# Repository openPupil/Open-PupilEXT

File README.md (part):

<div align="center">
  
</div><br/>
<div align="center">

</div>

<p align="center">
    &nbsp;
  
  </p>

# PupilEXT: flexible open-source platform for high resolution pupillometry in vision research

This repository provides the official implementation of a free pupillometry cross-platform (MacOS, Windows, Linux) system called PupilEXT proposed in the article *"PupilEXT: flexible open-source platform for high resolution pupillometry in vision research"* authored by Babak Zandi, Moritz Lode, Alexander Herzog, Georgios Sakas and Tran Quoc Khanh from the Technical University of Darmstadt.<br/>

PupilEXT can record eye images using a stereo camera system or a single camera to measure the pupil diameter in real-time. Additionally, it is possible to analyse externally-recorded images without connected cameras through the PupilEXT interface.<br/>

We aimed to provide a professional open-source pupillometry measurement platform, making an easy and inexpensive entry into pupil research for interdisciplinary research groups possible. PupilEXT integrates high-resolution industrial cameras from Basler. The pupil detection itself can be performed with one of the state-of-the-art open-source algorithms, Starburst [[1\]](#1), Swirski2D [[2\]](#2), ExCuSe [[3\]](#3), ElSe [[4\]](#4), PuRe [[5\]](#5), and PuReST [[6\]](#6).<br/>

-----

<div align="center">
<a style="font-weight:bold" href="https://www.frontiersin.org/articles/10.3389/fnins.2021.676220/abstract">[Paper]</a>
<a style="font-weight:bold" href="https://www.frontiersin.org/articles/10.3389/fnins.2021.676220/abstract">[Supplementary materials]</a>
</div>

-----

**Features of PupilEXT**

- [x]  High resolution pupillometry
- [x]  Real-time pupillometry
- [x]  Professional graphical user interface programmed with QT/C++
- [x]  Supporting stereo camera setups
- [x]  Supporting single camera setups
- [x]  Supporting Basler branded cameras (USB3). Tested with Basler acA2040-120um and acA1300-200um.
- [x]  Offline pupillometry with externally recorded images
- [x]  Cross-platform software: MacOS, Windows, Linux
- [x]  Intgrates six leading open-source pupil detection algorithms: Starburst [[1\]](#1), Swirski2D [[2\]](#2), ExCuSe [[3\]](#3), ElSe [[4\]](#4), PuRe [[5\]](#5), and PuReST [[6\]](#6).

For initial testing, we recommend using the provided demo datasets. See section 2.4 in this repository. Pay attention to the image playback speed under "preference" (see video tutorial) if you are on a laptop with low computational power.

**Questions?**

If you have new ideas, questions or want to discuss some extended topics, please use our discussion forum:
https://github.com/openPupil/Open-PupilEXT/discussions

**!! NEW 08/2024 !!: Release of PupilEXT v0.1.2**

A new branch called Experimental-Community-Version has been created (see https://github.com/openPupil/Open-PupilEXT/tree/Experimental-Community-Version) to support community additions. In this new branch PupilEXT v0.1.2 is available. Its maintainers are Gábor Bényei and Attila Boncsér. For further information check out the community [README](https://github.com/openPupil/Open-PupilEXT/tree/Experimental-Community-Version). More informations about the new features are also available here: https://github.com/openPupil/Open-PupilEXT/discussions/27

**!! NEW 04/2022 !!: A Python version of PupilEXT is now available.**

Note that the Python package of PupilEXT is currently in the experimental stage.

Link to the GitHub repo of PyPupilEXT: [https://github.com/openPupil/PyPupilEXT](https://github.com/openPupil/PyPupilEXT)

**!! NEW 12/2021 !!: Watch the video tutorials of PupilEXT that walk trough the interface**

**Tutorial 1/3:** Stereo camera recording<br/>
https://vimeo.com/564556788

**Tutorial 2/3:** Single camera recording<br/>
https://vimeo.com/564776313

**Tutorial 3/3:** External image analysis<br/>
https://vimeo.com/564778587

## 1. Overview
PupilEXT is a real-time pupillometry software whose graphical user interface is mainly programmed using C++ (QT. 5.15) and can be used to integrate high-resolution industrial cameras for online measurements. This Repository provides a guide on how to install, set up and use the system for pupillometry. Before using the PupilEXT framework, we recommend reading the work *"PupilEXT: flexible open-source platform for high resolution pupillometry in vision research"*.

### 1.1 Pupillometry setup configuations
With PupilEXT, you can detect the pupil diameter with three different setup configurations (see Figure). In the stereo camera configuration, the pupil diameter can be recorded directly in millimetres through an internal triangulation procedure. In the simplest case, only one camera must be connected for measuring the pupil diameter in pixels. The conversion from pixels to mm can then manually be performed using a circular reference object. If no camera is available, PupilEXT offers the possibility to load externally recorded images for offline analysis. The externally acquired images can be treated as a live feed, unlocking the full functionality of PupilEXT.

### 1.2 Hardware and software requirements
Depending on which setup configuration is used, additional hardware components must be purchased. Below is a list of components with which our demo system was built. In general, the USB3 Basler branded camera should be compatible with PupilEXT, as we use Pylon. For offline analysis with externally captured images, none of the listed hardware components is necessary. In any case, the [Pylon Camera Software Suite](https://www.baslerweb.com/de/produkte/software/basler-pylon-camera-software-suite/) from Basler must be installed on your system, as the drivers are needed to start PupilEXT, even if no camera(s) is connected. Check out our publication if you need additional information on how to build the hardware system.

**Components: Stereo camera configuration**

- 2 x Basler acA2040-120um (USB3 cameras)
- 2 x KOWA LM50JC3M2 (2/3" C-Mount lenses)
- 2 x Schneider IF 092 SH 27.0 (Filters)
- 2 x H06S Power I/O Cable
- 1 x STM32 Nucleo F767ZI or similar (Hardware trigger)
- 1 x IR-illumination (Recommended)

**Components: Single camera configuration**

- 1 x Basler acA2040-120um (USB3 cameras)
- 1 x KOWA LM50JC3M2 (2/3" C-Mount lense)
- 1 x Schneider IF 092 SH 27.0 (Red & NIR Color Filter)
- *1 x H06S Power I/O Cable (Optional)*
- *1 x STM32 Nucleo F767ZI or similar (Optional)*
- 1 x IR-illumination (Recommended)

We also tested the system with a Basler acA1300-200um camera model. To build a cheap pupillometry system, you can also have a look to the Basler dart series cameras, which cost approximatley 120 Euro. Note that we did not test PupilEXT with a dart series camera from Basler, but it should work as we use the standard Pylon library from Basler to communicate with the USB3 cameras.

Please use our discussion forum to share your ideas, setup and experience with PupilEXT with other community members:

https://github.com/openPupil/Open-PupilEXT/discussions

## 2. Getting started: The easy way
### 2.1. Installation on MacOS (macOS 10.15 or later)
The direct installation requires that you have macOS 10.15 or later installed on your machine. If this is not the case, you need to build PupilEXT from source, as the provided pre-build binaries in this section will only work on macOS 10.15 or later.

**Step 1: Download and install the Pylon Camera Softwware**

Download the Pylon Camera Software Suite (*.dmg) from the Basler Website:

https://www.baslerweb.com/de/vertrieb-support/downloads/downloads-software/

We tested PupilEXT with **Pylon 6.1.2.** (on Windows only **Pylon 6.0.1.** works, see the Win instructions below). If the Pylon installation does not start because of a security warning from Apple: Open the system preferences from macOS, click on "security & privacy" and press "Open Anyway" under the "General" tab. During the Pylon installation, ensure that a complete installation is carried out with the C++ binaries (Important!). For this, you need to choose the "custom" profile and activate all checkboxes under "Pylon runtime" and "SDKs". The Pylon library is necessary for PupilEXT to control and communicate with Basler branded cameras. The installation is also needed if no camera is connected, as the Basler drivers are part of the software.

Please test your Baslers camera(s) with the installed Pylon Viewer from Basler (see [Basler-Documentation: Pylon Viewer](https://docs.baslerweb.com/overview-of-the-pylon-viewer)) before driving the camera(s) with PupilEXT.

**Step 2: Download and run PupilEXT**

We have built and deployed PupilEXT for macOS 10.15 or later. You only need to download PupilEXT and open it. If you run into security warnings from Apple, you need to open the system preferences, click on "security & privacy" and then press "Open Anyway" under the "General" tab.

Download PupilEXT Version 0.1.1 Beta (MAC) from the release page of the project's GitHub repository:

https://github.com/openPupil/Open-PupilEXT/releases/tag/v0.1.1-beta

After you have downloaded the software, you can open the dmg file and run PupilEXT (see animation). We tested the program on a fresh installed Macbook Pro (Intel) with macOS Big Sur (Version 11.2.3) and a Mac Mini (Intel) with macOS Catalina (Version 10.15.7). If you run into issues, you need to build PupilEXT from source.

**Step 3: Testing with the demo datasets**

You can load the provided demo dataset (see section 2.4) into PupilEXT for initial testing and enjoying the features during offline analysis. We recommend watching the video tutorials (see section 2.5) of PupilEXT before using the provided eye images.

**Additional Information**

It should be noted that the PupilEXT software is not designed for the dark-mode of macOS, as the icons in the quick-toolbar are colored with black lines. Therefore, the icons will not be visible when running PupilEXT in dark mode. We recommend to use the software only in light-mode of macOS.

### 2.2. Installation on Windows 10 (64 bit)
**Step 1: Download and install the Pylon Camera Softwware**

Download the Pylon Camera Software Suite (*.exe) from the Basler Website:

https://www.baslerweb.com/de/vertrieb-support/downloads/downloads-software/

We tested PupilEXT with **Pylon 6.0.1.** on several fresh installed Windows 10 (64 bit) machines. Only the **Pylon 6.0.1.** version works with PupilEXT, as Windows is a diva. During the Pylon installation, ensure that a complete installation is carried out with the C++ binaries (Important!). For this, you need to choose the "custom" profile and activate all checkboxes under "Pylon runtime" and "SDKs". The Pylon library is necessary for PupilEXT to control and communicate with Basler branded cameras. The installation is also needed when no camera is connected, as the Basler drivers are part of the software.

Please test your camera with the installed Pylon Viewer from Basler (see [Basler-Documentation: Pylon Viewer](https://docs.baslerweb.com/overview-of-the-pylon-viewer)) before driving the cameras with PupilEXT.

**Step 2: Download and run PupilEXT**

For Windows, we have already built the software so that PupilEXT can simply be downloaded and will start without any further dependencies. Unpack the downloaded zip file and open PupilEXT.exe. It should run, as we tested it on several systems. However, if you run into unknown issues, you need to build PupilEXT from source (see instructions below).

Download PupilEXT Version 0.1.1 Beta (Windows) from the release page of the project's GitHub repository:

https://github.com/openPupil/Open-PupilEXT/releases/tag/v0.1.1-beta

**Step 3: Testing with the demo datasets**

You can load the provided demo dataset (see section 2.4) into PupilEXT for initial testing and enjoying the features during offline analysis. We recommend watching the video tutorials (see section 2.5) of PupilEXT before using the provided eye images.

### 2.3. Setup the microcontroller for the stereo camera configuration
A microcontroller is necessary if a real-time online pupil measurement should be carried out with a stereo camera system. The microcontroller has the task of generating a so-called electrical hardware-trigger, which is used to trigger the image acquisition on the camera (see [Basler-Documentation: Triggering](https://docs.baslerweb.com/triggered-image-acquisition)). The electrical hardware-trigger consists of a timed voltage signal of 3.3 V, which is applied to one of the camera's GPIO-Pins. If a sequence of images need to be acquired with a stable FPS, the hardware-trigger is a PWM-signal with a fixed frequency (see [Basler-Documentation: Trigger-Types](https://docs.baslerweb.com/trigger-selector) and [Basler-Documentation: GPIO Lines](https://docs.baslerweb.com/general-purpose-io-(gpio)-lines)). The advantage of acquiring images through a hardware-trigger signal is that the electrical signal can be connected parallel to both cameras, leading to a highly synchronized image recording. Synchronous image acquisition from both cameras is essential in a stereo camera system; otherwise, the conversion from pixels to mm is not reliable. The PupilEXT software uses a hardware-trigger from an external microcontroller (STM32 Nucleo) to acquire images from the stereo camera system. If you only want to use a single camera for pupil measurement, section 2.3 is not relevant for you.

In this way, the image capture process is as follows: The PupilEXT software sends a command (Protocol) to the microcontroller via USB (uart), aiming to start a logical hardware-trigger signal, which is transmitted from the microcontroller to the camera(s). The captured images are passed directly from the camera to PupilEXT via USB3. In continuous shooting, PupilEXT sends a command to let the microcontroller generate a continuous PWM signal, so there is no need for a single command for each trigger signal. This procedure is standard for all professional stereo camera systems. Hardware trigger signals can also be generated from the camera itself, but there is a risk that due to internal delays, the images will not be captured synchronously. Therefore, adding an external signal generator increases the stability of the system.

Since a standardised protocol between the PupilEXT software and the microcontroller is required, we have uploaded the corresponding embedded code in this repository in [``Misc/Microcontroller/STMNucleo_F767ZI``](Misc/Microcontroller/STMNucleo_F767ZI) and [``Misc/Microcontroller/STMNucleo_L432KC``](Misc/Microcontroller/STMNucleo_L432KC). The embedded projects were created using PlatformIO in Visual Studio Code. You can use either an STM32 Nucleo F767ZI or STM32 Nucleo L432KC microcontroller to flash our provided code to the microcontroller. Alternatively, you can use your own microcontroller, but you must pay attention to the communication protocol (see our publication).

We used the [Mbed 5 framework](https://os.mbed.com) for programming the STM32 Nucleo microcontroller. To simplify the flashing process for you, we highly recommend flashing the microcontroller using [Mbed Studio](https://os.mbed.com/studio/), as this is more user-friendly. Below is a step-by-step guide on how to flash the microcontroller with Mbed Studio.

**Step 1: Installation of Mbed Studio**

Download and install Mbed Studio. A free account is required before you can use it.

https://os.mbed.com/studio/

**Step 2: Flash the microcontroller**

Create a new project inside Mbed Studio and select your connected microcontroller from the list. In the following, we assume that you are using an STM32 Nucleo L432KC. Be sure to select Mbed OS 5 as a template from the list. You can select an empty programme as template. In the fresh created main.cpp file, paste the below-listed code and press the play button in Mbed Studio (Build profile: Release) to flash the microcontroller. If you are using an STM32 Nucleo F767ZI, use another code from the file [Misc/Microcontroller/STMNucleo_F767ZI/src/main.cpp](Misc/Microcontroller/STMNucleo_F767ZI/src/main.cpp), as the pin assignment is different.

```c++
#include "RawSerial.h"
#include "mbed.h"
#include <string>
#include <stdio.h>
#include <stdlib.h>

#define BUFF_LENGTH 15
#define BAUDRATE 115200

#define TX_PIN USBTX
#define RX_PIN USBRX

#define LED_PIN_1 LED1
#define Trigger_Pin PB_0

RawSerial pc(TX_PIN, RX_PIN);
volatile char rx_buf[BUFF_LENGTH];
Timer timer_Stopper;

DigitalOut LED_Green(LED_PIN_1);
DigitalOut Trigger(Trigger_Pin);
Ticker myTick;

// Global Values
char M_or_T; // T = Manually Trigger Mode
uint32_t Manually_Values[2];
uint32_t Automatic_Values[1];

volatile int flag_1 = 0;
volatile int flag_2 = 0;
int LED_ticker = 0;
int Threshold_Ticker = 0;
int STOP = 0;

void onTick() {
  LED_Green = !LED_Green;
  Trigger = !Trigger;
  LED_ticker++;
  if (LED_ticker >= 2 * Threshold_Ticker) {
    myTick.detach();
    LED_Green = 0;
    Trigger = 0;
  }
  if (STOP == 1) {
    myTick.detach();
    LED_Green = 0;
    Trigger = 0;
  }
}

void serialCb() {

  char *pch;
  pch = strtok((char *)rx_buf, "X");

  M_or_T = *pch;

  if (M_or_T == 'T') {
    pch = strtok(NULL, "X");
    Manually_Values[0] = atoi(pch);

    pch = strtok(NULL, "X");
    Manually_Values[1] = atoi(pch);
  }

  switch (M_or_T) {

  case 'T':
    Threshold_Ticker = Manually_Values[0];
    STOP = 0;
    LED_ticker = 0;
    myTick.attach_us(&onTick, Manually_Values[1]);
    break;

  case 'S':
    STOP = 1;
    break;

  default:
    break;
  }
}

void callback() {
  if (pc.getc() == '<') {
    pc.putc('<');
    for (int i = 0; i < 20; i++) {

      rx_buf[i] = pc.getc();

      if (rx_buf[i] != '>') {
        pc.putc(rx_buf[i]);
      }

      if (rx_buf[i] == '>') {
        pc.putc('>');
        pc.putc('\n');
        flag_1 = 1;
        break;
      }
    }
  }
}

int main() {
  LED_Green = 0;
  LED_ticker = 0;
  Trigger = 0;
  pc.baud(115200);
  pc.attach(&callback, Serial::RxIrq);
  pc.printf("Program started! \n");

  while (1) {
    if (flag_1 == 1) {
      serialCb();
      flag_1 = 0;
    }
  }
}
// STM32 Nucleo L432KC flashing code
// The provided code for the STM32 Nucleo is licensed under the MIT
// See the lincense file in this repostory:
// Microcontroller/STMNucleo_L432KC/LICENSE
```

**Step 3: Wire the components together:**

Plug the two purchased I/O cables (see section 1.2: Hardware requirements) into the I/O connector of camera 1 and 2. At the open end of the I/O cable are the respective 6 I/O lines of the camera. PIN 1, corresponding to Line 3 of the I/O cable can be used to apply a logical hardware trigger signal to the Basler acA2040-120um camera. Please read the documentation and warnings of your camera regarding the I/O PINs, otherwise you may damage your camera if the wrong voltage values are used (see [Basler-Manual: GPIO Lines](https://docs.baslerweb.com/general-purpose-io-(gpio)-lines)). Pay attention to the correct PIN numbers of the I/O connector and check the camera's documentation to see which I/O PIN is the correct one for your case: https://docs.baslerweb.com/aca2040-120um

Connect the respective I/O line of camera 1 and camera 2 in parallel with the trigger PIN on the microcontroller. If you have used our embedded code to flash the microcontroller, it is PIN ``PB_0`` on the STM32 Nucleo L432KC or PIN ``PC_6`` on the STM32 Nucleo F767ZI. You can check where the PIN is located on the board by checking the Mbed webpage:

Pinout sketch STM32 Nucleo L432KC: https://os.mbed.com/platforms/ST-Nucleo-L432KC/

Pinout sketch STM32 Nucleo F767ZI: https://os.mbed.com/platforms/ST-Nucleo-F767ZI/

We recommend verifying that the microcontroller has been successfully flashed. To do this, you can enter the following command ``<TX10X1000000>`` (Protocol: ``<T X Count_of_Trigger X Time_Trigger_on_us>``) in a serial monitor (Baudrate: 115200). For example, when using the protocol ``<TX5X1000000>``. This command will flash the green led 5 times at 1 Hz. For this, copy&paste **everything inside the highlighted area `` ``** to the serial monitor. As serial communication interace, either use the integrated serial monitor of Mbed Studio or another one like HWMonitor or [CoolTerm](https://freeware.the-meiers.org). The command ``<TX10X1000000>`` should start a flashing green LED (10 times) on the microcontroller, with a turn-on time of 1000000 microseconds in each cycle. Since the hardware-trigger PIN of the microcontroller is "connected" to the LED, it signifies that the PC-to-microcontroller communication and the signal generation are working. Additionally, the trigger signal can be measured using an oscilloscope.

Once the microcontroller's correct operation has been checked, the cameras can be connected to the microcontroller and the PC via USB. Simultaneously, the hardware trigger PIN of the microcontroller should be connected in parallel with GPIO PINs of camera 1 and camera 2. Do not forget to connect the GND line of the camera to the GND PIN of the microcontroller. The figure in [``Misc/img/PupilEXT_Measuremtn_Setups.png``](Misc/img/PupilEXT_Measuremtn_Setups.png) illustrates the setup of a stereo camera configuration. After the connection has been made correctly, the PupilEXT software can be started to begin measuring the pupil diameter through the stereo camera system.

### 2.4. Demo dataset for offline analysis
We provide three different recorded datasets containing eye images that can be analysed using PupilEXT. This should give users the possibility to work directly with the software PupilEXT. The first two data sets were recorded using a single camera. Data set number 3 was recorded with a stereo camera system and is used in the video tutorial of PupilEXT (see section 2.5). The images were acquired directly with PupilEXT, as we offer the feature to record images for later offline measurement of the pupil diameter without connected cameras. The data set is suitable for playing around with PupilEXT and getting a first impression.

We stored the demo data in the TUdatalib repository: https://tudatalib.ulb.tu-darmstadt.de/handle/tudatalib/2929

| Description | Preview | Download-Link | File-size |
| :---         |     :---:      |          :---- |         :---: |
| Recorded with a single camera under natural light with a filter in front of the lens. Dataset is without a calibration file. |  | [Download dataset 1](https://tudatalib.ulb.tu-darmstadt.de/bitstream/handle/tudatalib/2929/Single_camera_recording_1.zip?sequence=1&isAllowed=y) | 1.2 Gb |
| Recorded with a single camera under natural light without a filter in front of the lens. Dataset is without a calibration file |  | [Download dataset 2](https://tudatalib.ulb.tu-darmstadt.de/bitstream/handle/tudatalib/2929/Single_camera_recording_2.zip?sequence=2&isAllowed=y) | 600 Mb |
| Recorded using a stereo camera system with IR-illumination and a filter in front of the lens. Calibration files are available and loaded to PupilEXT (see instructions below). |  | [Part 1](https://tudatalib.ulb.tu-darmstadt.de/bitstream/handle/tudatalib/2929/Stereo_camera_recording_Part_1.zip?sequence=3&isAllowed=y)<br>[Part 2](https://tudatalib.ulb.tu-darmstadt.de/bitstream/handle/tudatalib/2929/Stereo_camera_recording_Part_2_CAM0.zip?sequence=4&isAllowed=y)<br>[Part 3](https://tudatalib.ulb.tu-darmstadt.de/bitstream/handle/tudatalib/2929/Stereo_camera_recording_Part_3_CAM1.zip?sequence=5&isAllowed=y) | ~10 Gb |

**Instructions on how to use the stereo camera demo data:**
The data set is divided into three parts. Please download all three files first. Part 1 (``Stereo_camera_recording_Part_1``) is the main folder containing the two subfolders ``Calibration_Files`` and ``Stereo_Images``. The ``Stereo_Images`` subfolder is currently empty and needs to be filled with the demo images of ``cam 0`` and ``cam 1``. For this, download Part 2 (``Stereo_camera_recording_Part_2_CAM0``) and Part 3 (``Stereo_camera_recording_Part_3_CAM1``). Unzip the two folders and rename the folder ``Stereo_camera_recording_Part_2_CAM0`` to ``0`` and also rename folder ``Stereo_camera_recording_Part_3_CAM1`` to ``1``. Move the renamed folder ``0`` and ``1`` into the subfolder ``Stereo_Images`` of the main folder ``Stereo_camera_recording_Part_1`` (Part 1). In PupilEXT, you only need to choose the subfolder Stereo_Imagesas image source. The folder ``0`` and ``1`` will be automatically assigned to ``cam 0`` and ``cam 1``. The individual calibration files are in the subfolder ``Calibration_Files``. You only need to choose the stereo calibration file and not the single calibration files for each camera (see video tutorials).

**Note on externally acquired images**

When loading images to PupilEXT for offline analysis, take care of proper file names. For example, if you label your files with sequenced numbers such as 1.png, 2.png, 3.png, 4.png, 5.png, 6.png, 7.png, 8.png, 9.png, 10.png, 11.png, you will run into issues, as the order of the images will be changed to 1.png, 10.png, 11.png, 2.png, ...

It is better to label the images with 001.png, with the time stamp in milliseconds or similar. If you recorded the images with PupilEXT, everything is labelled correctly as we use the timestamp in milliseconds as filenames. The provided demo datasets are recorded with PupilEXT.

### 2.5 Notes about the pupil detection acuracy

The pupil detection can be determined in PupilEXT with one of the six open-source pupil detection methods Starburst [[1\]](#1), Swirski2D [[2\]](#2), ExCuSe [[3\]](#3), ElSe [[4\]](#4), PuRe [[5\]](#5), and PuReST [[6\]](#6). The respective algorithm can be selected directly within the pupillometry interface. A pupil measurement's accuracy depends on the applied detection algorithm if the image quality and composition are ideal. Each pupil detection algorithm has a certain number of parameters (constants) that the user must set.  For instance, at least the minimum or maximum possible pupil diameter must be adjusted, which can depend on the image's resolution. In PupilEXT, we offer the possibility to adjust the parameters of an applied detection algorithm, leading to more freedom in increasing the measurement accuracy. The original publications' standard parameters are usually not ideal for all measurement settings and should be adjusted if the detection rate is not good enough.

The accuracy can also be increased by selecting a specific region of interest (ROI) in the image. In this way, the algorithm no longer needs to perform pupil detection over the entire image. A smaller ROI size also reduces the calculation time, allowing a higher framerate in real-time measurements. We provide different preset settings for the algorithms` parameters which are dependent on the used ROI size. However, we highly recommend using the PuRe or PuReST algorithm, as it needs only three parameters. Furthermore, these two pupil detection algorithms are considered both the fastest and accurate in the literature and are part of the amazing open-source eye-tracking software EyeRecToo [[7\]](#7). According to our preliminary investigations, the Swirski algorithm can provide better results, as it does not downscale the image before a pupil detection. The downside is that it needs a higher calculation time and has a higher number of parameters. There is the risk that the parameters do not match the image composition, leading to poor pupil detection accuracy.

### 2.5. How to use PupilEXT ?
Three videos are provided to illustrate the handling and the features of the *PupilEXT* software. The first video introduces the *PupilEXT* software in stereo vision mode. The second video shows how the pupillometry can be carried out by using a single camera. The third video shows how pupillometry can be carried out with existing eye images without connected cameras.

**Video Tutorial 1 – Stereo camera setup:** https://vimeo.com/564556788

**Video Tutorial 2 – Single camera setup:** https://vimeo.com/564776313

**Video Tutorial 3 – Offline analysis:** https://vimeo.com/564778587

## 3. Build PupilEXT from source: The advanced way

If you would like to contribute to this project, extend PupilEXT with custom functions, or the provided binaries do not work on your machine, building PupilEXT on your machine is necessary. The annoying part of compiling C++ projects is the integration of third-party libraries into a project. For this, you have three options: (i) use a system package manager like brew to download and build third-party libraries; (ii) download the libraries without a package manager and build it; (iii) integrating the libraries directly into the project.

If you want to stick with option (ii) you are a professional C++ developer and do not need this tutorial. Option (i) is preferable if you have several C++ projects on your machine and want to share the libraries between the projects, saving disc space (see section 3.1 and section 3.2). However, we highly recommend option (iii), which has the advatange that the integration of thirdparty libraries is fully automated(see section 3.0). You should have intermediate knowledge of C++ programming and CMake before you follow this tutorial, as we provide no warranty.

PupilEXT need the following libraries: Boost 1.75-0_2, Ceres 2.0.0, Eigen 3.3.9, OpenCV 4.5.1_3, QT 5.15.0, [spii](https://github.com/PetterS/spii), tbb, pylon 6.

**Important Note 1:** When using Boost@1.76 or higher, you will run into compiling issues, as boost::math::sign will not work, which is used by one of the pupil detection methods.

**Important Note 2:** If you want to follow option (i) or (ii)  you need to remove the 'vcpkg.json' file and the '.vscode' folder.

### 3.0 Build PupilEXT with vcpkg manifest (recommended)

The PupilEXT project contains a vcpkg.json file in which all the required C++ libraries are defined. To download and build the libraries, we use the package management software vcpkg (https://vcpkg.io/en/index.html). We have placed the vcpkg GitHub repository as a submodule under [``3rdparty/vcpkg``](3rdparty/vcpkg), meaning that the required libraries will be downloaded automatically to the PupilEXT project folder, regardless of your system. This has the advantage that the PupilEXT folder can be easily deleted when the C++ libraries are no longer needed. However, as the libraries are downloaded and built, care must be taken to ensure that at least 6 GB are available on the disc for the PupilEXT folder (on windows ~13 GB). However, the QT library and the Pylon drivers for the cameras will not be managed via vcpkg, so they have to be downloaded and installed manually (see step 1 and 2).

**Step 1: Download and install the latest Pylon Camera Softwware**

Download the Pylon Camera Software Suite (*.dmg-File) from the Basler Website:
https://www.baslerweb.com/de/vertrieb-support/downloads/downloads-software/

Important: You need to modify the [`Open-PupilEXT/cmake/FindPylon.cmake`](https://github.com/openPupil/Open-PupilEXT/blob/main/cmake/FindPylon.cmake) file according to the Pylon version before you start to build the project. Please read the latest post in this discussion for more information: https://github.com/openPupil/Open-PupilEXT/discussions/21

**Step 2: Download and install QT**

Download the QT from the website. Please install QT 5.15:
https://www.qt.io/download-open-source?hsCtaTracking=9f6a2170-a938-42df-a8e2-a9f0b1d6cdce%7C6cb0de4f-9bb5-4778-ab02-bfb62735f3e5

QT 6 or higher is currently not supported.

Update: On Mac QT 6.7.2 seems to work either.

**Step 3: Clone this repository**

Type into your terminal the following command

```shell
git clone --recurse-submodules https://github.com/openPupil/Open-PupilEXT.git
```

The ``--recurse-submodules`` option is important, as vcpkg is a submodule. Without this option, the 3rdparty folder will not contain vcpkg packet manager.

Open the ``CMakeLists.tx`` file in the PupilEXT root and change the following line, according to your installed QT, user name and cpu archteure.

```Cmake
set(QT_VERSION 5.15.2) # Change the version according to your installation
set(USER_NAME_MAC papillon) # Only necessary for macOS users, skip if you are on WIN

set(CMAKE_OSX_ARCHITECTURES_VALUE "arm64") # Options for cmake: arm64, x86_64 - needed for oneTBB
set(VCPKG_VALUE_ARCH "arm64-osx") # Options for vcpkg: arm64-osx, x64-osx
```

**Step 4: Decide which Editor to use**

Depending on which editor is used, the procedure is slightly different. We have created a summary of how to proceed if you want to use [Visual Studio Code](https://code.visualstudio.com), [CLion](https://www.jetbrains.com/clion/promo/?source=google&medium=cpc&campaign=11964013627&gclid=Cj0KCQjw-NaJBhDsARIsAAja6dPFpHIXmFeKhVv0qheHTki-WmG5DepDCzR0iWuYQqAXEM1eEAELpy4aApLsEALw_wcB) or [QT Creator](https://www.qt.io/product/development-tools) to start PupilEXT (see the below option 1 to 4).

**Option 1: Build with Visual Studio Code**

First, the following extensions must be downloaded in the editor for the procedure to work:

(1) C++ extension: https://marketplace.visualstudio.com/items?itemName=ms-vscode.cpptools

(2) Cmake extension: https://marketplace.visualstudio.com/items?itemName=twxs.cmake

(3) Cmake Tools extension: https://code.visualstudio.com/docs/cpp/cmake-linux

Then open the ``.vscode/settings.json`` file in the cloned PupilEXT folder with a text editor. The entry ``"VCPKG_TARGET_TRIPLET": "x64-osx"`` must be changed to ``"VCPKG_TARGET_TRIPLET": "x64-windows-static-md"`` if you have a Windows operating system. If you are on a Mac, leave the entry as it is. However, when using a Mac with apple silicon (e.g. M3 Max or similar) you need to change this entry to ``"VCPKG_TARGET_TRIPLET": "arm64-osx"``. Open the project folder with Visual Studio Code and build the project. If you press build for the first time, it may take a little longer, as the required libraries are downloaded and will build automatically. Make sure that you have enough disc space on your machine.

**Option 2: Build with CLion**

Open the project folder with CLion. Then some settings have to be made. For this, go to ``CLion > Preferences > Build, Execution, Deployment`` in the toolbar. Choose Debug and type in the Cmake options the following command:

```shell
-DVCPKG_TARGET_TRIPLET=x64-osx -DCMAKE_TOOLCHAIN_FILE=3rdparty/vcpkg/scripts/buildsystems/vcpkg.cmake
```
Note that `x64-osx` must be changed to `x64-windows-static-md`, if you are on a Windows machine. However, when using a Mac with apple silicon (e.g. M3 Max or similar) you need to change this entry to ``"VCPKG_TARGET_TRIPLET": "arm64-osx"``. Next, choose for the build directory, the following folder: ``build``. This is very important, as the CMakeLists.txt is adjusted to find the libraries in a folder called ``build``. By default, CLion will build the project in a folder called ``cmake-build-debug``, which will not work with the current CMakeLists.txt. Press okay and build the project. The C++ libraries will be downloaded and build automatically for you. The first run will take some time. Make sure that you have enough disc space.

**Option 3: Build with QT Creator**

QTCreator also supports CMake, which means that PupilEXT can also be opened there. As with CLion, only the following options need to be added:

```shell
-DVCPKG_TARGET_TRIPLET=x64-osx -DCMAKE_TOOLCHAIN_FILE=3rdparty/vcpkg/scripts/buildsystems/vcpkg.cmake
```

Note that `x64-osx` must be changed to `x64-windows-static-md`, if you are on a Windows machine. However, when using a Mac with apple silicon (e.g. M3 Max or similar) you need to change this entry to `"VCPKG_TARGET_TRIPLET": "arm64-osx"`. Next, choose for the build directory, the following folder: ``build``.

**Option 4: Build from terminal**

Open your terminal and type the following commands if you are on a Mac:

```shell
cd Open-PupilEXT

mkdir build

cd build

cmake .. -G "Unix Makefiles" -DCMAKE_BUILD_TYPE=Release -DVCPKG_TARGET_TRIPLET=x64-osx -DCMAKE_TOOLCHAIN_FILE=3rdparty/vcpkg/scripts/buildsystems/vcpkg.cmake

cmake --build . --config Release

./src/PupilEXT
```
Note that you need to change `-DVCPKG_TARGET_TRIPLET=x64-osx` to `"VCPKG_TARGET_TRIPLET": "arm64-osx"` if you have an apple silicon.

If you are on Windows 10  use these commands (not tested, but should be similar):

```shell
cd Open-PupilEXT

mkdir build

cd build

cmake .. -DCMAKE_BUILD_TYPE=Release -DVCPKG_TARGET_TRIPLET=x64-windows-static-md -DCMAKE_TOOLCHAIN_FILE=3rdparty/vcpkg/scripts/buildsystems/vcpkg.cmake

cmake --build . --config Release
```
Then, the executable will be available here ``/Open-PupilEXT-main/build/src/PupilEXT``.

Note, the option ``-DCMAKE_TOOLCHAIN_FILE=3rdparty/vcpkg/scripts/buildsystems/vcpkg.cmak`` makes sure to use the submodule as package manager and download the C++ libraries defined in the vcpkg.json file. The ``-DVCPKG_TARGET_TRIPLET=x64-os`` option is necessary to let vcpkg know which triplet your need. On Windows you need to change the tripplet to ``-DVCPKG_TARGET_TRIPLET=x64-windows-static-md``.

### 3.1 How to build from source on MacOS (outdated)

**Step 1: Download and install the latest Pylon Camera Softwware**

Download the Pylon Camera Software Suite (*.dmg-File) from the Basler Website:
https://www.baslerweb.com/de/vertrieb-support/downloads/downloads-software/

**Step 2: Download and install QT**

Download the QT from the website. Please install QT 5.15:
https://www.qt.io/download-open-source?hsCtaTracking=9f6a2170-a938-42df-a8e2-a9f0b1d6cdce%7C6cb0de4f-9bb5-4778-ab02-bfb62735f3e5

**Step 3: Install the package manager homebrew**

Homebrew is a package manager for macOS with which C++ libraries can be installed relatively easily via the terminal. Instructions on how to install Homebrew can be found here: https://brew.sh

To install homebrew , you can enter the following command in the macOS terminal.

```shell
/bin/bash -c "$(curl -fsSL https://raw.githubusercontent.com/Homebrew/install/HEAD/install.sh)"
```

**Step 4: C++ Libraries**

Now install the necessary C++ libraries for PupilEXT through homebrew. The Ceres library will be installed by OpenCV.

```shell
brew install cmake
brew install boost
brew install Eigen
brew install glog
brew install tbb
brew install opencv
```

**Step 5: Download and build the spii library**

An additional library called spii must be downloaded and built manually. This library is not included in Homebrew. First, go to the following GitHub repository and download it:

https://github.com/PetterS/spii

Open the downloaded folder ``spii-master`` with [CLion](https://www.jetbrains.com/clion/). By default, CLion is set to debug mode. Therefore, the release option must be added. For this, go to CLion > Preferences > Build, Execution, Deployment in the toolbar. Then press the + symbol under CMake, which automatically adds the release mode. You can then switch to release in the top right-hand corner of the CLion toolbar. You can now build the project. Simply go to Build > Build Project.

**Step 6: Add spii to PupilEXT**

The source files of PupilEXT are located here in Github under the PupilEXT folder. Download it from GitHub and create a new folder called ``PupilEXT/external`` in the main PupilEXT folder. In ``external/`` add another new folder called ``spii/``.

In the folder ``PupilEXT/external/spii`` you need to copy the spii build created in step 5. First go to ``spii-master/cmake-build-release`` and copy the folder ``spii-master/cmake-build-release/lib`` to ``spii-master``. Then copy all files inside the ``spii-master/`` folder into ``PupilEXT/external/spii``.

**Step 7: Build PupilEXT from source**

Now, open the PupilEXT project with CLion. In the file ``PupilEXT/CMakeLists.txt`` the paths must be updated so that the installed C++ libraries from step 4 can be correctly recognised. The complete content in ``PupilEXT/CMakeLists.txt`` can be removed and replaced by the following code snippet:

```cmake
cmake_minimum_required(VERSION 3.15)
project(PupilEXT)
set(CMAKE_CXX_STANDARD 17)

set(CMAKE_AUTOMOC ON)
set(CMAKE_AUTORCC ON)
set(CMAKE_AUTOUIC ON)

if(CMAKE_VERSION VERSION_LESS "3.7.0")
    set(CMAKE_INCLUDE_CURRENT_DIR ON)
endif()

set(CMAKE_MODULE_PATH ${CMAKE_MODULE_PATH} ${PROJECT_SOURCE_DIR}/cmake)
set(CMAKE_PREFIX_PATH ${CMAKE_PREFIX_PATH} "/Users/papillon/Qt/5.15.2/clang_64")
set(CMAKE_PREFIX_PATH ${CMAKE_PREFIX_PATH} "/usr/local/Cellar/glog/0.4.0")
set(CMAKE_PREFIX_PATH ${CMAKE_PREFIX_PATH} "/usr/local/include/gflags")
set(CMAKE_PREFIX_PATH ${CMAKE_PREFIX_PATH} "/Library/Frameworks/pylon.framework")
set(CMAKE_PREFIX_PATH ${CMAKE_PREFIX_PATH} "/usr/local/Cellar/tbb/2020_U3_1")

set(SPII_INSTALL_DIR "/Users/papillon/Desktop/PupilEXT/external/spii")
set(spii_INCLUDE_DIRS ${SPII_INSTALL_DIR}/include)
set(GLOG_INCLUDE_DIR "/usr/local/Cellar/glog/0.4.0/include")
set(EIGEN_INCLUDE_DIR "/usr/local/Cellar/eigen/3.3.9/include/eigen3/Eigen")
set(EIGEN3_INCLUDE_DIR "/usr/local/include/eigen3")
SET("OpenCV_DIR" "/usr/local/Cellar/opencv/4.5.1_3/lib/cmake/opencv4")
SET("TBB_DIR" "/usr/local/Cellar/tbb/2020_U3_1/lib/cmake/TBB")

if(CMAKE_BUILD_TYPE STREQUAL Debug)
    set(CMAKE_PREFIX_PATH ${CMAKE_PREFIX_PATH} "/usr/local/share/ceres-solver")
else()
    set(CMAKE_PREFIX_PATH ${CMAKE_PREFIX_PATH} "/usr/local/share/ceres-solver")
endif()

set(PYLON_HOME "/Library/Frameworks/pylon.framework")
set(PYLON_INCLUDE_DIR "/Library/Frameworks/pylon.framework/Headers")

find_package(Qt5 COMPONENTS Widgets Concurrent SerialPort Charts Svg PrintSupport REQUIRED)
find_package(OpenCV REQUIRED PATHS "/usr/local/Cellar/opencv/4.5.1_3")
find_package(Boost 1.72 REQUIRED)
find_package(TBB REQUIRED PATHS "${PROJECT_SOURCE_DIR}/external/tbb")
find_package(Eigen3 REQUIRED )
find_package(Ceres REQUIRED)
find_package(Pylon REQUIRED)
find_package(OpenGL REQUIRED)

set(TBB_LIBRARY_DEBUG "/usr/local/include/tbb")
set(TBB_LIBRARY_RELEASE "/usr/local/include/tbb")

find_library (spii_LIBRARY_RELEASE
        spii
        PATHS ${SPII_INSTALL_DIR}/lib/)
find_library (meschach_LIBRARY_RELEASE
        meschach
        PATHS ${SPII_INSTALL_DIR}/lib/)
if (spii_LIBRARY_RELEASE AND meschach_LIBRARY_RELEASE)
    set(spii_LIBRARIES ${spii_LIBRARY_RELEASE} ${meschach_LIBRARY_RELEASE})
else()
    set(spii_LIBRARIES "")
endif()

include_directories(${Qt5Core_INCLUDE_DIRS}
        ${OpenCV_INCLUDE_DIRS}
        ${Boost_INCLUDE_DIRS}
        ${TBB_INCLUDE_DIR}
        ${spii_INCLUDE_DIRS}
        ${EIGEN_INCLUDE_DIR}
        ${CERES_INCLUDE_DIRS}
        ${PYLON_INCLUDE_DIR}
        "singleeyefitter")

add_subdirectory (src)
add_subdirectory (singleeyefitter)

message(STATUS "")
message(STATUS "spii_LIBRARIES:\"${spii_LIBRARIES}\"")
message(STATUS "--- Include directories ---" )
message(STATUS " QT5Core_INCLUDE_DIRS: ${Qt5Core_INCLUDE_DIRS}" )
message(STATUS " OpenCV_INCLUDE_DIRS: ${OpenCV_INCLUDE_DIRS}" )
message(STATUS " Boost_INCLUDE_DIRS: ${Boost_INCLUDE_DIRS}" )
message(STATUS " TBB_INCLUDE_DIRS: ${TBB_INCLUDE_DIR}" )
message(STATUS " spii_INCLUDE_DIRS: ${spii_INCLUDE_DIRS}" )
message(STATUS " EIGEN_INCLUDE_DIR: ${EIGEN_INCLUDE_DIR}" )
message(STATUS " CERES_INCLUDE_DIRS: ${CERES_INCLUDE_DIRS}" )
message(STATUS " PYLON_INCLUDE_DIRS: ${PYLON_INCLUDE_DIR}" )
message(STATUS "---------------------------" )
message(STATUS "")
set(CMAKE_CXX_FLAGS "${CMAKE_CXX_FLAGS} -march=native -O3")
```

Make sure that all folder paths in the ``CMakelist.txt`` are adapted to your system. For instance, the path ``/Users/papillonmac/Qt/5.15.0/clang_64`` must be changed with the name of your user name and your specific QT version installed on your PC.

----

The described changes to the Pylon library in this section can be skipped, as we included in the updated CMakelists.txt the following code for macOS:

```cmake
set(PYLON_INCLUDE_DIR ${PYLON_INCLUDE_DIR} "/Library/Frameworks/pylon.framework/Headers")
    set(PYLON_INCLUDE_DIR ${PYLON_INCLUDE_DIR} "/Library/Frameworks/pylon.framework/Headers/GenICam")
```

**Old description (not needed):**

The last step is to change something in the Pylon library; otherwise, the library will not be found properly. For this, open the following folder on your computer: /Library/Frameworks/pylon.framework/Versions/A/Headers/GenICam. All files in this folder must be copied to /Library/Frameworks/pylon.framework/Versions/A/Headers.

---

Now, you should be able to start PupilEXT properly in CLion. Please remember to use the **release** option as in step 5; otherwise, PupilEXT will run in debug mode and will be significantly slower.

### 3.2 How to build from source on Windows 10

**Step 1: Install Visual Studio 2019**

C++ MFC must be installed during the installation. Additionally, the English language package must be included. Visual Studio can be downloaded from the following page:

https://visualstudio.microsoft.com/downloads/

**Step 2: Download and install the Pylon Camera Software**

Download the Pylon Camera Software Suite (*.dmg) from the Basler Website:
https://www.baslerweb.com/de/vertrieb-support/downloads/downloads-software/

**Step 3: Download and install QT**

Download the QT from the website. Please install QT 5.15. You need to add ``msvc2017_64`` during the installation:
https://www.qt.io/download-open-source?hsCtaTracking=9f6a2170-a938-42df-a8e2-a9f0b1d6cdce%7C6cb0de4f-9bb5-4778-ab02-bfb62735f3e5

**Step 4: Install the C++ package manager**

There is a C++ package manager from Microsoft for Windows, making it relatively easy to download libraries. For this, install the program ``vcpkg``. The instructions on how to install the package manager can be found on the following page:

https://docs.microsoft.com/de-de/cpp/build/install-vcpkg?view=msvc-160&tabs=windows

To install vcpkg type in your console the following commands:

```shell
git clone https://github.com/Microsoft/vcpkg.git
cd vcpkg
.\bootstrap-vcpkg.bat
```

**Step 5: Install the C++ Librarys**

Go to your console and use the following commands to install the C++ libraries:

```shell
vcpkg install boost:x64-windows
vcpkg install Eigen:x64-windows
vcpkg install ceres:x64-windows
vcpkg install glog:x64-windows
vcpkg install opencv:x64-windows
vcpkg install tbb:x64-windows
```

**Step 6: Download and build spii**

The spii library is not included in vcpkg. You need to build it manually. First, go to the following page and download the spii library from GitHub:

https://github.com/PetterS/spii

Then [CLion](https://www.jetbrains.com/clion/) can be used to open and build the spii library. Make sure that you use the 64 bit architecture. Then the folder ``spii-master/cmake-build-release/lib`` can be copied into the main folder ``spii-master/``. Lastly, copy the files inside ``spii-master/`` to ``PupilEXT/external/spii``.

**Step 7: Prepare the CMakelists file**

You can add the following code snippet to the file ``PupilEXT/CMakeLists.txt``  to let PupilEXT recognize vcpkg libraries. Make sure to adjust the appropriate paths and version numbers.

```cmake
cmake_minimum_required(VERSION 3.15)
project(PupilEXT)

set(CMAKE_AUTOMOC ON)
set(CMAKE_AUTORCC ON)
set(CMAKE_AUTOUIC ON)
if(CMAKE_VERSION VERSION_LESS "3.7.0")
    set(CMAKE_INCLUDE_CURRENT_DIR ON)
endif()

set(CMAKE_MODULE_PATH ${CMAKE_MODULE_PATH} ${PROJECT_SOURCE_DIR}/cmake)
set(CMAKE_PREFIX_PATH ${CMAKE_PREFIX_PATH} "C:/Qt/Qt5.13.1/5.10.0/msvc2017_64")
set(CMAKE_PREFIX_PATH ${CMAKE_PREFIX_PATH} "C:/vcpkg/installed/x64-windows")
set(GLOG_INCLUDE_DIR "C:/vcpkg/installed/x64-windows/include")
if(CMAKE_BUILD_TYPE STREQUAL Debug)
    set(CMAKE_PREFIX_PATH ${CMAKE_PREFIX_PATH} "C:/vcpkg/installed/x64-windows/debug")
else()
    set(CMAKE_PREFIX_PATH ${CMAKE_PREFIX_PATH} "C:/vcpkg/installed/x64-windows/include")
endif()

set(TBB_INCLUDE_DIR "C:/vcpkg/installed/x64-windows/include/tbb")
set(SPII_INSTALL_DIR "${PROJECT_SOURCE_DIR}/external/spii")
set(spii_INCLUDE_DIRS ${SPII_INSTALL_DIR}/include)
set(PYLON_HOME "C:/Program Files/Basler/pylon 6/Development/")
find_package(Qt5 COMPONENTS Widgets SerialPort Charts Svg PrintSupport REQUIRED)
find_package(OpenCV REQUIRED)
find_package(Boost 1.72 REQUIRED)
find_package(TBB REQUIRED PATHS "${PROJECT_SOURCE_DIR}/external/tbb")
find_package(Eigen3 REQUIRED )
find_package(Ceres CONFIG REQUIRED)
find_package(Pylon REQUIRED)
set(TBB_LIBRARY_DEBUG "${PROJECT_SOURCE_DIR}/external/tbb/lib/intel64")
set(TBB_LIBRARY_RELEASE "${PROJECT_SOURCE_DIR}/external/tbb/lib/intel64")

find_library (spii_LIBRARY_RELEASE
        spii
        PATHS ${SPII_INSTALL_DIR}/lib/)
find_library (meschach_LIBRARY_RELEASE
        meschach
        PATHS ${SPII_INSTALL_DIR}/lib/)
if (spii_LIBRARY_RELEASE AND meschach_LIBRARY_RELEASE)
    set(spii_LIBRARIES ${spii_LIBRARY_RELEASE} ${meschach_LIBRARY_RELEASE})
else()
    set(spii_LIBRARIES "")
endif()

include_directories(${Qt5Core_INCLUDE_DIRS}
        ${OpenCV_INCLUDE_DIRS}
        ${Boost_INCLUDE_DIRS}
        ${TBB_INCLUDE_DIR}
        ${spii_INCLUDE_DIRS}
        ${EIGEN_INCLUDE_DIR}
        ${CERES_INCLUDE_DIRS}
        ${PYLON_INCLUDE_DIR}
        "singleeyefitter")

add_subdirectory (src)
add_subdirectory (singleeyefitter)

message(STATUS "")
message(STATUS "spii_LIBRARIES:\"${spii_LIBRARIES}\"")
message(STATUS "--- Include directories ---" )
message(STATUS " QT5Core_INCLUDE_DIRS: ${Qt5Core_INCLUDE_DIRS}" )
message(STATUS " OpenCV_INCLUDE_DIRS: ${OpenCV_INCLUDE_DIRS}" )
message(STATUS " Boost_INCLUDE_DIRS: ${Boost_INCLUDE_DIRS}" )
message(STATUS " TBB_INCLUDE_DIRS: ${TBB_INCLUDE_DIR}" )
message(STATUS " spii_INCLUDE_DIRS: ${spii_INCLUDE_DIRS}" )
message(STATUS " EIGEN_INCLUDE_DIR: ${EIGEN_INCLUDE_DIR}" )
message(STATUS " CERES_INCLUDE_DIRS: ${CERES_INCLUDE_DIRS}" )
message(STATUS " Pylon_INCLUDE_DIRS: ${PYLON_INCLUDE_DIR}" )
message(STATUS "---------------------------" )
message(STATUS "")
set(CMAKE_CXX_FLAGS "${CMAKE_CXX_FLAGS} -march=native -O3")
```

**Step 8: Environment variables**

Add the bin folder of vcpkg and QT to the environment variables of Windows; otherwise, the libraries will not be found.

**Step 9: Build PupilEXT with CLion**

Before the programme can be build, some settings must be made in CLion:

1) File > Setting > Build, Execution, Deoployment > CMAKE under CMAKE options add the following parameter: --config Debug -DVCPKG_TARGET_TRIPLET=x64-windows -DCMAKE_TOOLCHAIN_FILE=C:/vcpkg/scripts/buildsystems/vcpkg.cmake

2) Then press the plus sign to add the release configuration. Add the following parameters to the release options:: --config Release -DVCPKG_TARGET_TRIPLET=x64-windows -DCMAKE_TOOLCHAIN_FILE=C:/vcpkg/scripts/buildsystems/vcpkg.cmake

3) The build architecture must be changed to amd64 under Toolchain, as the vcpkg libraries were also installed with 64 bit.

Next, the bin folders must be added to the path of CLION, as these are independent of the Windows environment variables. Under Run > Edit Configuration the paths to VCPKG and QT can be added:

```shell
C:\Qt\Qt5.13.1\5.10.0\msvc2017_64\bin
C:\vcpkg\installed\x64-windows\bin
```

In order to start the programme, the SPII DLL must be added to ``PupilEXT\cmake-build-debug\src``. If everything has been done correctly, you can now press Start and the software should open without any issues.

## 4. Misc

**Camera emulation**
For debugging porpuses, the Pylon SDK supports emulating camera devices that are then displayed as physical cameras in the PupilExt software. To activate the camera emulation, the system environment variable "PYLON_CAMEMU" needs to be set. The number of available emulator devices can be controlled by exporting the PYLON_CAMEMU environment variable. For example, ``export PYLON_CAMEMU=2``.

## 5. Known issues
see here https://github.com/openPupil/Open-PupilEXT/issues

## 6. Citation
Please consider to cite our work if you find this repository or our results useful for your research:

B. Zandi, M. Lode, A. Herzog, G. Sakas, and T. Q. Khanh, “PupilEXT: Flexible Open-Source Platform for High-Resolution Pupillometry in Vision Research,” Front. Neurosci., vol. 15, Jun. 2021, doi: 10.3389/fnins.2021.676220.

```bib
@Article{10.3389/fnins.2021.676220,
AUTHOR = {Zandi, Babak and Lode, Moritz and Herzog, Alexander and Sakas, Georgios and Khanh, Tran Quoc},
TITLE = {PupilEXT: Flexible Open-Source Platform for High-Resolution Pupillometry in Vision Research},
JOURNAL = {Frontiers in Neuroscience},
VOLUME={15},
PAGES={603},
YEAR={2021},
URL={https://www.frontiersin.org/article/10.3389/fnins.2021.676220},
DOI={10.3389/fnins.2021.676220},
ISSN={1662-453X}}
```

## 7. References
<a id="1">**[1]**</a> Dongheng Li and Derrick J. Parkhurst. Starburst: A robust algorithm for video-based eye tracking. IEEE Computer Society Conference on Computer Vision and Pattern Recognition (CVPR), September 2005.

<a id="2">**[2]**</a> Lech Swirski, Andreas Bulling, and Neil Dodgson. Robust real-time pupil tracking in highly off-axis images. In Proceedings - 2012 ACM Symposium on Eye Tracking Research and Applications (ETRA), pages 173–176, 2012.

<a id="3">**[3]**</a> Wolfgang Fuhl, Thomas Kübler, Katrin Sippel, Wolfgang Rosenstiel, and Enkelejda Kasneci. Excuse: robust pupil detection in real-world scenarios. In International Conference on Computer Analysis of Images and Patterns, pages 39–51. Springer, 2015.

<a id="4">**[4]**</a> Wolfgang Fuhl, Thiago C. Santini, Thomas Kübler, and Enkelejda Kasneci. ElSe: Ellipse selection for robust pupil detection in real-world environments. In Proceedings - 2016 ACM Symposium on Eye Tracking Research and Applications (ETRA), volume 14, pages 123–130, 2016.

<a id="5">**[5]**</a> Thiago Santini, Wolfgang Fuhl, and Enkelejda Kasneci. PuRe: Robust pupil detection for real-time pervasive eye tracking. Computer Vision and Image Understanding, 170:40–50, 2018.

<a id="6">**[6]**</a> Thiago Santini, Wolfgang Fuhl, and Enkelejda Kasneci. PuReST: Robust pupil tracking for real-time pervasive eye tracking. In Proceedings - 2018 ACM Symposium on Eye Tracking Research and Applications (ETRA). ACM, 2018.

<a id="7">**[7]**</a> Thiago Santini, Wolfgang Fuhl, David Geisler and Enkelejda Kasneci. EyeRecToo: Open-source Software for Real-time Pervasive Head-mounted Eye Tracking. VISIGRAPP 2017.

## 8. Open source projects inside PupilEXT
PupilEXT integrates several open source libraries. This document provides a list of the used libraries. The respective licenses of the libraries are provided as *.txt file in in the subfolder `3rdparty/PupilEXT_Third_Party_Licenses`.

### List of Pupil Detection Libraries

<a id="EyeRecToo" href="https://github.com/tcsantini/EyeRecToo"><b>EyeRecToo</b></a> is an open-source eye tracking software for head-mounted eye tracker and integrates the most advanced state-of-the-art open-source pupil detection algorithms.  We used the implementation of the EyeRecToo’s pupil class and the integrated detection methods for PupilEXT. (License: Copyright (c) 2018, Thiago Santini / University of Tübingen). **License:** For academic and non-commercial use only ([Link License](https://github.com/tcsantini/EyeRecToo/blob/master/LICENSE) | [Project Page](https://github.com/tcsantini/EyeRecToo)).

<a id="PuRe" href="https://www.sciencedirect.com/science/article/abs/pii/S1077314218300146?via%3Dihub"><b>PuRe</b></a> Thiago Santini, Wolfgang Fuhl, Enkelejda Kasneci, PuRe: Robust pupil detection for real-time pervasive eye tracking. *Computer Vision and Image Understanding*. **2018**, ISSN 1077-3142. https://doi.org/10.1016/j.cviu.2018.02.002. Part of the [EyeRecToo](https://github.com/tcsantini/EyeRecToo) software. Copyright (c) 2018, Thiago Santini, University of Tübingen. **License:** For non-commercial purposes only ([Link](https://github.com/tcsantini/EyeRecToo/blob/master/EyeRecToo/src/pupil-detection/PuRe.h)).

<a id="PuReST" href="https://github.com/tcsantini/EyeRecToo/blob/master/EyeRecToo/src/pupil-tracking/PuReST.h"><b>PuReST</b></a> Thiago Santini, Wolfgang Fuhl, Enkelejda Kasneci. PuReST: Robust pupil tracking for real-time pervasive eye tracking. *Symposium on Eye Tracking Research and Applications (ETRA)*. **2018**. https://doi.org/10.1145/3204493.3204578. Part of the [EyeRecToo](https://github.com/tcsantini/EyeRecToo) software. Copyright (c) 2018, Thiago Santini, University of Tübingen. **License:** For non-commercial purposes ([Link](https://github.com/tcsantini/EyeRecToo/blob/master/EyeRecToo/src/pupil-tracking/PuReST.h)).

<a id="ElSe" href="https://dl.acm.org/doi/10.1145/3204493.3204578"><b>ElSe</b></a> Wolfgang Fuhl, Thiago Santini, Thomas Kübler, Enkelejda Kasneci. ElSe: Ellipse Selection for Robust Pupil Detection in Real-World Environments. *ETRA 2016 : Eye Tracking Research and Application.* **2016.** Part of the [EyeRecToo](https://github.com/tcsantini/EyeRecToo) software. Copyright (c) 2018, Thiago Santini, University of Tübingen. **License:** For non-comercial use only ([Link](https://github.com/tcsantini/EyeRecToo/blob/master/EyeRecToo/src/pupil-detection/ElSe.h)).

<a id="ExCuSe" href="https://link.springer.com/chapter/10.1007/978-3-319-23192-1_4"><b>ExCuSe</b></a> Wolfgang Fuhl, Thomas Kübler, Katrin Simpel, Wolfgang Rosenstiel, Enkelejda Kasneci. ExCuSe: Robust Pupil Detection in Real-World Scenarios. *CAIP 2015 : Computer Analysis of Images and Patterns*. **2015**. Part of the [EyeRecToo](https://github.com/tcsantini/EyeRecToo) software. Copyright (c) 2018, Thiago Santini, University of Tübingen. **License:** For non-comercial use only ([Link](https://github.com/tcsantini/EyeRecToo/blob/master/EyeRecToo/src/pupil-detection/ExCuSe.h)).

<a id="Starburst" href="https://ieeexplore.ieee.org/document/1565386"><b>Starburst</b></a> Dongheng Li, Winfield, D., Parkhurst, D. J. Starburst: A hybrid algorithm for video-based eye tracking combining feature-based and model-based approaches. in *2005 IEEE Computer Society Conference on Computer Vision and Pattern Recognition (CVPR’05) - Workshops* vol. 3 79–79 (IEEE, 2005). https://doi.org/10.1109/CVPR.2005.531. Based on the [cvEyeTracker](https://github.com/thirtysixthspan/cvEyeTracker) Version 1.2.5 implementation. **License:** GNU General Public License ([Link](https://github.com/thirtysixthspan/cvEyeTracker/blob/master/ransac_ellipse.cpp))

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
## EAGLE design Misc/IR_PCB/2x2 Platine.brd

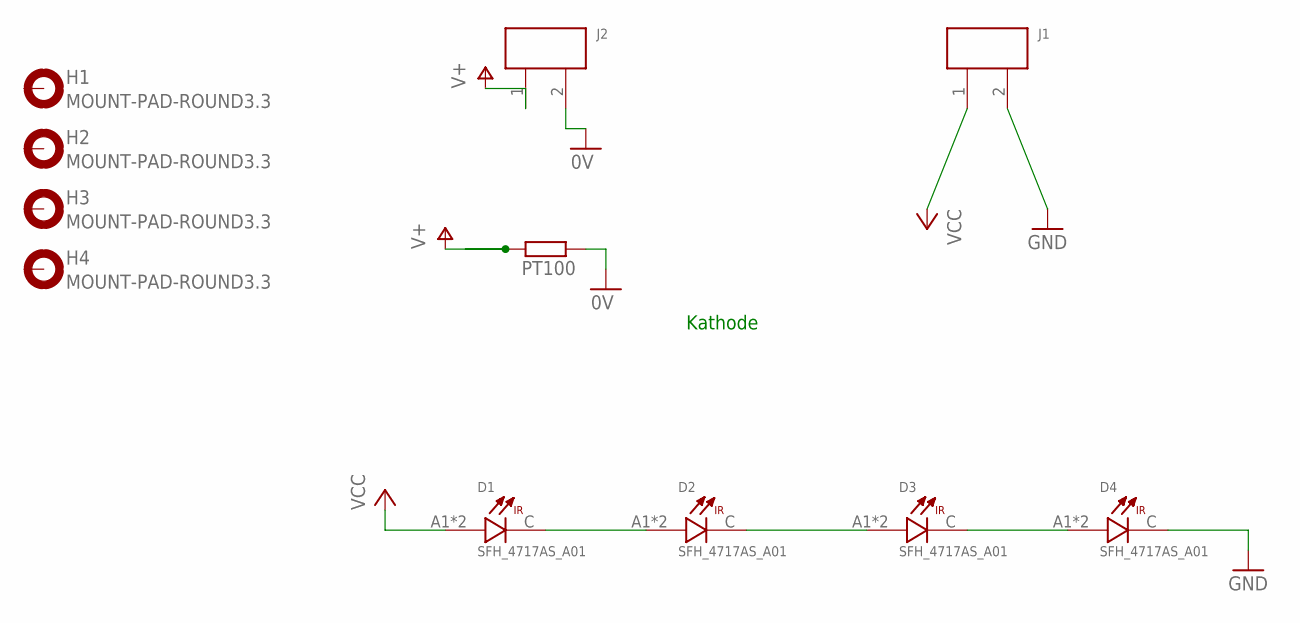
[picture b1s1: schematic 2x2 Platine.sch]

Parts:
D1, D2, D3, D4: SFH_4717AS_A01; LED_SFH_4717AS_A01
H1, H2, H3, H4: MOUNT-PAD-ROUND3.3; 3,3-PAD
J1, J2: 662102145021
PT100: R-EU_R0603; R0603

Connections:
0V: J2.2 (1), PT100.1
GND: D4.C, J1.2 (1)
unnamed: D1.C, D2.A1 (A), D2.A2 (A)
unnamed: D2.C, D3.A1 (A), D3.A2 (A)
unnamed: D3.C, D4.A1 (A), D4.A2 (A)
V+: J2.1 (2), PT100.2
VCC: D1.A1 (A), D1.A2 (A), J1.1 (2)

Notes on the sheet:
Kathode

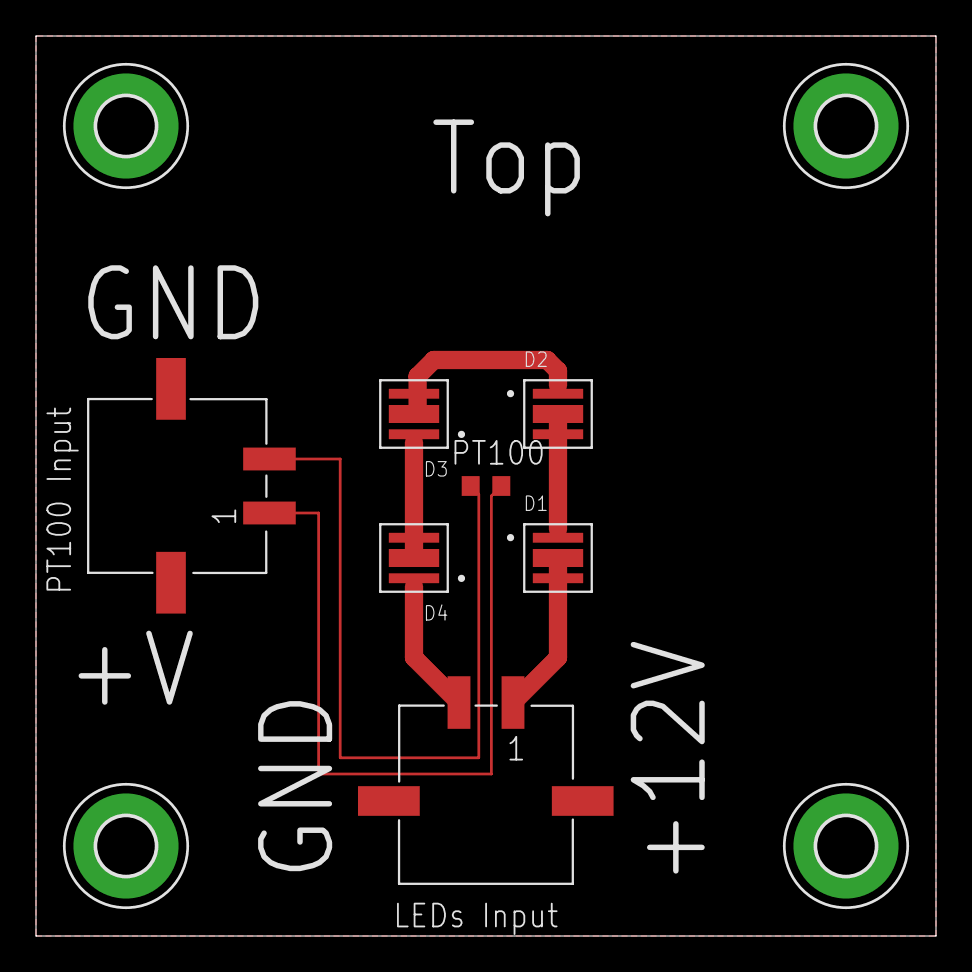
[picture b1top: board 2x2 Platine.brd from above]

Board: 1 copper layer, 50.0 x 50.0 mm, 11 parts (0 on the bottom side), 7 nets.

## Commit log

2021-03-05 Update README.md
    Update README
2021-03-09 Update Readme: license added
2021-03-09 Update Readme: License links added
2021-03-24 Init with content
2021-03-28 Logo added to readme
2021-03-28 Style update readme
2021-03-28 Logo size updated
2021-03-28 Readme Logo change
2021-04-13 Added pupil detection references to the readme
2021-04-13 Readme update
2021-04-15 Added the Matlab folder for pupil data evaluation
2021-04-15 Removed test file
2021-06-18 Update readme: added vimeo tutorial links
2021-06-19 Updated readme: new position of the tutorial links
2021-06-19 Update readme: style
2021-06-19 Update readme: new bullet in known issues
2021-06-19 Update readme: fixed pylon version to 6.0.1 (win)
2021-06-19 Update manual
2021-06-21 Fixed ROI placement (ML)
    The ROI position was not loaded correctly from the preferences. Additionally, the text in the about menu was updated.
2021-06-21 Update readme: added links to new beta
2021-07-03 Update dl links
2021-07-23 Update readme: added the DOI in the header
2021-09-01 New project structure
2021-09-02 CMakeLists.txt updated [Tested on macOS]
2021-09-02 Added Win10 compatibility
2021-09-04 Added auto build
2021-09-05 CMake: added custom vars, boost
2021-09-05 update vcpkg submodule
2021-09-05 CMakelists update
2021-09-06 New section 3.0 for developer
2021-09-06 Update readme (section 3.0)
2021-09-06 Added transparent logo
2021-09-06 updated image
2021-09-07 Readme fixed typos
2021-09-09 Update readne
2023-01-19 Update stereoCameraSettingsDialog.cpp
    (runtime * 60000000) resulted in integer overflow for any runtime higher than approximately 35 if cast into an integer. Putting the division in brackets this should stay as a double during division, 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
2023-03-11 Added community README file, and a link to it in the main README file.
2023-04-06 PupilEXT Experimental-Community-Version, unstable, first commit
2023-04-06 Fix #1, initialize imagePlaybackControlDialog to null so that null checking guard function catches it when disconnecting the camera.
2023-04-11 Fix #2, playback speed was not set in imageReader after updating playback speed. Set noDelay to false in case FPS is greater than 0. (#17)
2023-04-11 Fix #4. Fix #54. (#56)
2023-04-11 Fix #14. Show correct framerates on Single Camera Settings dialog (#57)
2023-04-12 Fix #3. Calibration and Sharpness windows no longer crash. (#59)
2023-04-12 Fix #55. Set imagePlaybackControlDialog, campTempMonitor pointers to null (#60)
2023-05-26 9 store pupil detection roi in a rational way and discretize only upon setting it in pupildetectioncpp (#75)
2023-06-06 Handle Pylon emulated camera binning exception (#78)
2023-06-06 Resolve #10. (#79)
2023-06-06 22 allow jumping to specific frame number or timestamp in imageplaybackcontroldialog (#80)
2023-07-25 87 crash upon opening an empty folder as image recording folder (#90)
2023-07-27 Add Linux configuration to CMake and include additional pylon directo… (#95)
2023-08-04 Added markdown file with basic Q&A/FAQ help for build environment setup troubleshooting
2023-08-10 94 document build process and clarify possible problems and their solutions in documentation (#96)
2023-08-10 12 automatic parametrization setting and its overlay should be only changeable and visible when automatic parametrization is on (#97)
2023-08-17 86 add freeze image functionality (#102)
2023-08-22 Temporarily removed mirrored camera option from GUI and commented out… (#104)
2023-08-22 Added option in settings to adapt to OS light/dark mode changes. (#105)
2023-10-08 32 custom widget to show image acquisition roi size and offset settings graphically in camera settings dialogs (#111)
2023-10-08 110 make documentation for remote control commands and startup parameters (#114)
2023-10-08 refined microcontroller instructions
2023-11-06 Fix #113. Test for emulated camera when setting hardware related conf… (#115)
2024-04-02 Added automatic csv path assignment upon image folder open, and added… (#118)
2024-04-02 Added drag and drop feature to open an image recording directory (#119)
2024-04-16 18 imageplaybackcontroldialog stops at a few frames earlier when naturally stopped at playback end (#121)
2024-04-16 Fixes 120. Handle selected stereo folders not containing images, sele… (#125)
2024-04-17 Usability changes to pupil detection configuration settings (#126)
2024-04-17 Resolved problems related to image or data recordings when existing data is found (#128)
2024-04-22 Added remote message logging feature. Also added offline event log ve… (#129)
2024-04-23 Solved issue #6 and committed several minor changes related to other issues (#130)
2024-04-24 Additional fixes related to output serialization and usability (#131)
2024-07-15 Implemented the feature, on two levels: first on a try-catch then che… (#132)
2024-07-19 Added experiment integration example codes and updated markdown manua… (#136)
2024-07-23 Added camera positioning guide functionality. Added icons for Setting… (#141)
2024-07-30 58 memory leak related to sharpness dialog (#153)
2024-07-30 Simplified workflow for camera serial connection and hardware trigger… (#151)
2024-08-06 Addressing issues 162, 161, 160, 159, 158, 157, 156, 155, 154, 143, 116, 69 (#163)
2024-08-06 Fix sharpness worker not being cleaned up after closing sharpness dialog (#169)
2024-08-07 Could not reproduce but fixed another (#170)
2024-08-13 Resolving issues #168, #171, #172, #174, and also added skeleton code… (#175)
2024-08-22 181 minor gui fixes to fit the program for proper display on macos (#195)
2024-08-24 196 adjustments before finishing release v012 beta (#198)
2024-08-25 196 adjustments before finishing release v012 beta (#199)
2024-08-26 Corrected license section (#201)
2024-09-21 Add oneTBB as a submodule
2024-09-21 Update CMake configuration in VSCode settings
2024-09-21 Update oneTBB submodule to the latest commit
2024-09-21 Add oneTBB as a submodule and ensure vcpkg points to the correct commit
2024-09-21 Exclude .cache directory from version control
2024-09-21 Fixed TBB error and added support for apple silicon (#58)
    * Add oneTBB as a submodule
    * Update CMake configuration in VSCode settings
    * Update oneTBB submodule to the latest commit
    * Update oneTBB submodule to the latest commit
    * Add oneTBB as a submodule and ensure vcpkg points to the correct commit
    * Exclude .cache directory from version control
2024-09-22 Refactor TBB library handling in CMakeLists.txt
2024-09-22 Removed manual build of oneTBB

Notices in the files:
README.md:
6. Citation:
Please consider to cite our work if you find this repository or our results useful for your research:
B. Zandi, M. Lode, A. Herzog, G. Sakas, and T. Q. Khanh, “PupilEXT: Flexible Open-Source Platform for High-Resolution Pupillometry in Vision Research,” Front. Neurosci., vol. 15, Jun. 2021, doi: 10.3389/fnins.2021.676220.
@Article{10.3389/fnins.2021.676220,
AUTHOR = {Zandi, Babak and Lode, Moritz and Herzog, Alexander and Sakas, Georgios and Khanh, Tran Quoc},
TITLE = {PupilEXT: Flexible Open-Source Platform for High-Resolution Pupillometry in Vision Research},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
